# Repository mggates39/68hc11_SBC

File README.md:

# 68hc11_SBC   [![Badge License]][License]
Building a Single Board Computer around the MC68HC11.  Specifically the XC68HC11A1FN - A38P8642.  It will include my first attempt with [KiCad](https://www.kicad.org/) designing a PCB

[![Button Manual]][Manual]
[![Button Memory]][Memory]

Software built with [TASM](https://www.ticalc.org/archives/files/fileinfo/250/25051.html)

Run in the [68HC11 Simulator](http://www.hc11.demon.nl/thrsim11/thrsim11.htm)

<!----------------------------------[ File links ]--------------------------------->

[License]: LICENSE
[Manual]: Documentation/Reference/68hc11%20Technical%20Manual.pdf
[Memory]: Documentation/Memory%20Map.md

<!----------------------------------[ Badges ]--------------------------------->

[Badge License]: https://img.shields.io/badge/License-GPL3-015d93.svg?style=for-the-badge&labelColor=blue

<!---------------------------------[ Buttons ]--------------------------------->

[Button Manual]: https://img.shields.io/badge/User_Manual-4285F4?style=for-the-badge&logoColor=white&logo=GitBook
[Button Memory]: https://img.shields.io/badge/Memory_Map-0F9D58?style=for-the-badge&logoColor=white&logo=Fitbit

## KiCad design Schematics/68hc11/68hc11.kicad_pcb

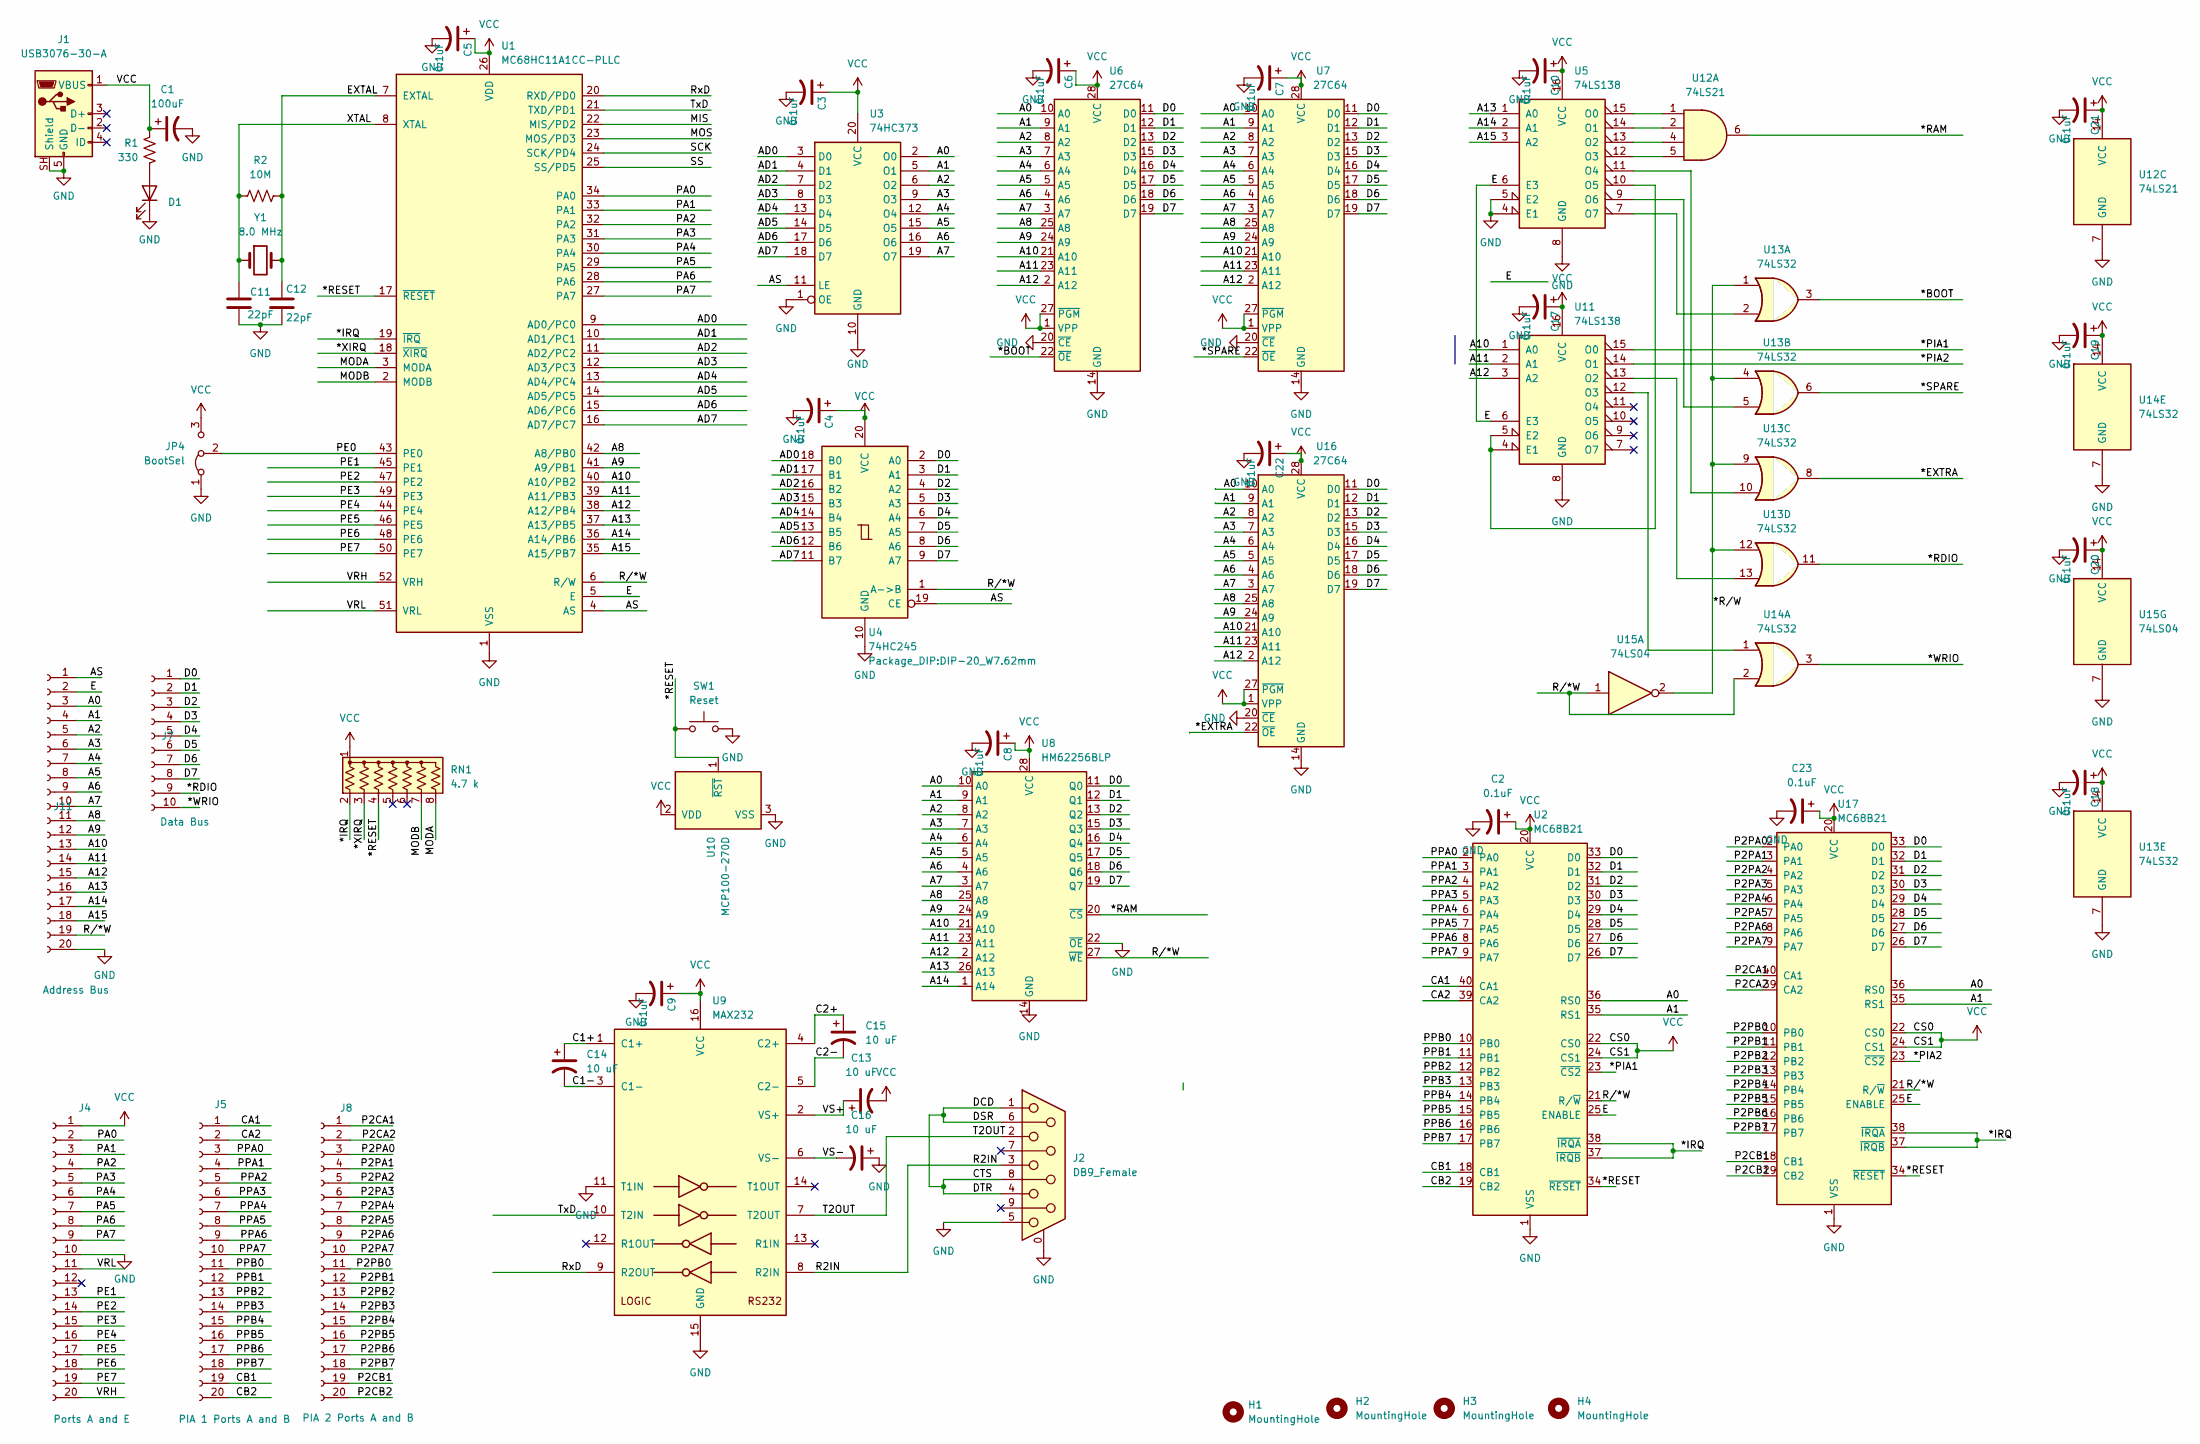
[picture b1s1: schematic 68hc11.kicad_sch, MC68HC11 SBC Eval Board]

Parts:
C1: 100uF; CP_Radial_D5.0mm_P2.00mm
C2, C3, C4, C5, C6, C7, C8, C9, C10, C17, C18, C19, C20, C21, C22, C23: 0.1uF; C_Disc_D3.0mm_W2.0mm_P2.50mm
C11, C12: 22pF; C_Disc_D3.0mm_W1.6mm_P2.50mm
C13, C14, C15, C16: 10 uF; CP_Radial_D5.0mm_P2.00mm
D1: LED; LED_D5.0mm
H1, H2, H3, H4: MountingHole; MountingHole_2.5mm
J1: USB3076-30-A; USB_Micro_B_Female_10118193-0001LF
J2: DB9_Female; DSUB-9_Male_Horizontal_P2.77x2.84mm_EdgePinOffset4.94mm_Hou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
J4: Ports A and E; PinSocket_1x20_P2.54mm_Vertical
J5: PIA 1 Ports A and B; PinSocket_1x20_P2.54mm_Vertical
J7: Data Bus; PinSocket_1x10_P2.54mm_Vertical
J8: PIA 2 Ports A and B; PinSocket_1x20_P2.54mm_Vertical
J11: Address Bus; PinSocket_1x20_P2.54mm_Vertical
JP4: BootSel; PinHeader_1x03_P2.54mm_Vertical
R1: 330; R_Axial_DIN0204_L3.6mm_D1.6mm_P5.08mm_Horizontal
R2: 10M; R_Axial_DIN0204_L3.6mm_D1.6mm_P5.08mm_Horizontal
RN1: 4.7 k; R_Array_SIP8
SW1: Reset; SW_PUSH_6mm
U1: MC68HC11A1CC-PLLC; PLCC-52_THT-Socket
U2, U17: MC68B21; DIP-40_W15.24mm
U3: 74HC373; DIP-20_W7.62mm
U4: 74HC245; DIP-20_W7.62mm
U5, U11: 74LS138; DIP-16_W7.62mm
U6, U7, U16: 27C64; DIP-28_W15.24mm
U8: HM62256BLP; DIP-28_W15.24mm
U9: MAX232; DIP-16_W7.62mm
U10: MCP100-270D; TO-92
U12: 74LS21; DIP-14_W7.62mm
U13, U14: 74LS32; DIP-14_W7.62mm
U15: 74LS04; DIP-14_W7.62mm
Y1: 8.0 MHz; Crystal_HC49-4H_Vertical

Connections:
/*BOOT: U6.22 (~OE), U13.3
/*EXTRA: U13.8, U16.22 (~OE)
/*IRQ: RN1.2 (R1), U1.19 (~IRQ), U2.37 (~IRQB), U2.38 (~IRQA), U17.37 (~IRQB), U17.38 (~IRQA)
/*PIA1: U2.23 (~CS2), U11.15 (O0)
/*PIA2: U11.14 (O1), U17.23 (~CS2)
/*RAM: U8.20 (~CS), U12.6
/*RDIO: U13.11
/*RESET: RN1.4 (R3), SW1.1, U1.17 (~RESET), U2.34 (~RESET), U10.1 (~RST), U17.34 (~RESET)
/*R/W: U13.1, U13.4, U13.9, U13.12, U15.2
/*SPARE: U7.22 (~OE), U13.6
/*WRIO: U14.3
/*XIRQ: RN1.3 (R2), U1.18 (~XIRQ)
/A0: J11.3, U2.36 (RS0), U3.2 (O0), U6.10 (A0), U7.10 (A0), U8.10 (A0), U16.10 (A0), U17.36 (RS0)
/A1: J11.4, U2.35 (RS1), U3.5 (O1), U6.9 (A1), U7.9 (A1), U8.9 (A1), U16.9 (A1), U17.35 (RS1)
/A2: J11.5, U3.6 (O2), U6.8 (A2), U7.8 (A2), U8.8 (A2), U16.8 (A2)
/A3: J11.6, U3.9 (O3), U6.7 (A3), U7.7 (A3), U8.7 (A3), U16.7 (A3)
/A4: J11.7, U3.12 (O4), U6.6 (A4), U7.6 (A4), U8.6 (A4), U16.6 (A4)
/A5: J11.8, U3.15 (O5), U6.5 (A5), U7.5 (A5), U8.5 (A5), U16.5 (A5)
/A6: J11.9, U3.16 (O6), U6.4 (A6), U7.4 (A6), U8.4 (A6), U16.4 (A6)
/A7: J11.10, U3.19 (O7), U6.3 (A7), U7.3 (A7), U8.3 (A7), U16.3 (A7)
/A8: J11.11, U1.42 (A8/PB0), U6.25 (A8), U7.25 (A8), U8.25 (A8), U16.25 (A8)
/A9: J11.12, U1.41 (A9/PB1), U6.24 (A9), U7.24 (A9), U8.24 (A9), U16.24 (A9)
/A10: J11.13, U1.40 (A10/PB2), U6.21 (A10), U7.21 (A10), U8.21 (A10), U11.1 (A0), U16.21 (A10)
/A11: J11.14, U1.39 (A11/PB3), U6.23 (A11), U7.23 (A11), U8.23 (A11), U11.2 (A1), U16.23 (A11)
/A12: J11.15, U1.38 (A12/PB4), U6.2 (A12), U7.2 (A12), U8.2 (A12), U11.3 (A2), U16.2 (A12)
/A13: J11.16, U1.37 (A13/PB5), U5.1 (A0), U8.26 (A13)
/A14: J11.17, U1.36 (A14/PB6), U5.2 (A1), U8.1 (A14)
/A15: J11.18, U1.35 (A15/PB7), U5.3 (A2)
/AD0: U1.9 (AD0/PC0), U3.3 (D0), U4.18 (B0)
/AD1: U1.10 (AD1/PC1), U3.4 (D1), U4.17 (B1)
/AD2: U1.11 (AD2/PC2), U3.7 (D2), U4.16 (B2)
/AD3: U1.12 (AD3/PC3), U3.8 (D3), U4.15 (B3)
/AD4: U1.13 (AD4/PC4), U3.13 (D4), U4.14 (B4)
/AD5: U1.14 (AD5/PC5), U3.14 (D5), U4.13 (B5)
/AD6: U1.15 (AD6/PC6), U3.17 (D6), U4.12 (B6)
/AD7: U1.16 (AD7/PC7), U3.18 (D7), U4.11 (B7)
/AS: J11.1, U1.4 (AS), U3.11 (LE), U4.19 (CE)
/C1+: C14.1, U9.1 (C1+)
/C1-: C14.2, U9.3 (C1-)
/C2+: C15.1, U9.4 (C2+)
/C2-: C15.2, U9.5 (C2-)
/CA1: J5.1, U2.40 (CA1)
/CA2: J5.2, U2.39 (CA2)
/CB1: J5.19, U2.18 (CB1)
/CB2: J5.20, U2.19 (CB2)
/CTS: J2.1, J2.4, J2.6, J2.8
/D0: J7.1, U2.33 (D0), U4.2 (A0), U6.11 (D0), U7.11 (D0), U8.11 (Q0), U16.11 (D0), U17.33 (D0)
/D1: J7.2, U2.32 (D1), U4.3 (A1), U6.12 (D1), U7.12 (D1), U8.12 (Q1), U16.12 (D1), U17.32 (D1)
/D2: J7.3, U2.31 (D2), U4.4 (A2), U6.13 (D2), U7.13 (D2), U8.13 (Q2), U16.13 (D2), U17.31 (D2)
/D3: J7.4, U2.30 (D3), U4.5 (A3), U6.15 (D3), U7.15 (D3), U8.15 (Q3), U16.15 (D3), U17.30 (D3)
/D4: J7.5, U2.29 (D4), U4.6 (A4), U6.16 (D4), U7.16 (D4), U8.16 (Q4), U16.16 (D4), U17.29 (D4)
/D5: J7.6, U2.28 (D5), U4.7 (A5), U6.17 (D5), U7.17 (D5), U8.17 (Q5), U16.17 (D5), U17.28 (D5)
/D6: J7.7, U2.27 (D6), U4.8 (A6), U6.18 (D6), U7.18 (D6), U8.18 (Q6), U16.18 (D6), U17.27 (D6)
/D7: J7.8, U2.26 (D7), U4.9 (A7), U6.19 (D7), U7.19 (D7), U8.19 (Q7), U16.19 (D7), U17.26 (D7)
/E: J11.2, U1.5 (E), U2.25 (ENABLE), U5.6 (E3), U11.6 (E3), U17.25 (ENABLE)
/EXTAL: C12.1, R2.1, U1.7 (EXTAL), Y1.2
/MIS: U1.22 (MIS/PD2)
/MODA: RN1.8 (R7), U1.3 (MODA)
/MODB: RN1.7 (R6), U1.2 (MODB)
/MOS: U1.23 (MOS/PD3)
/P2CA1: J8.1, U17.40 (CA1)
/P2CA2: J8.2, U17.39 (CA2)
/P2CB1: J8.19, U17.18 (CB1)
/P2CB2: J8.20, U17.19 (CB2)
/P2PA0: J8.3, U17.2 (PA0)
/P2PA1: J8.4, U17.3 (PA1)
/P2PA2: J8.5, U17.4 (PA2)
/P2PA3: J8.6, U17.5 (PA3)
/P2PA4: J8.7, U17.6 (PA4)
/P2PA5: J8.8, U17.7 (PA5)
/P2PA6: J8.9, U17.8 (PA6)
/P2PA7: J8.10, U17.9 (PA7)
/P2PB0: J8.11, U17.10 (PB0)
/P2PB1: J8.12, U17.11 (PB1)
/P2PB2: J8.13, U17.12 (PB2)
/P2PB3: J8.14, U17.13 (PB3)
/P2PB4: J8.15, U17.14 (PB4)
/P2PB5: J8.16, U17.15 (PB5)
/P2PB6: J8.17, U17.16 (PB6)
/P2PB7: J8.18, U17.17 (PB7)
/PA0: J4.2, U1.34 (PA0)
/PA1: J4.3, U1.33 (PA1)
/PA2: J4.4, U1.32 (PA2)
/PA3: J4.5, U1.31 (PA3)
/PA4: J4.6, U1.30 (PA4)
/PA5: J4.7, U1.29 (PA5)
/PA6: J4.8, U1.28 (PA6)
/PA7: J4.9, U1.27 (PA7)
/PE0: JP4.2 (C), U1.43 (PE0)
/PE1: J4.13, U1.45 (PE1)
/PE2: J4.14, U1.47 (PE2)
/PE3: J4.15, U1.49 (PE3)
/PE4: J4.16, U1.44 (PE4)
/PE5: J4.17, U1.46 (PE5)
/PE6: J4.18, U1.48 (PE6)
/PE7: J4.19, U1.50 (PE7)
/PPA0: J5.3, U2.2 (PA0)
/PPA1: J5.4, U2.3 (PA1)
/PPA2: J5.5, U2.4 (PA2)
/PPA3: J5.6, U2.5 (PA3)
/PPA4: J5.7, U2.6 (PA4)
/PPA5: J5.8, U2.7 (PA5)
/PPA6: J5.9, U2.8 (PA6)
/PPA7: J5.10, U2.9 (PA7)
/PPB0: J5.11, U2.10 (PB0)
/PPB1: J5.12, U2.11 (PB1)
/PPB2: J5.13, U2.12 (PB2)
/PPB3: J5.14, U2.13 (PB3)
/PPB4: J5.15, U2.14 (PB4)
/PPB5: J5.16, U2.15 (PB5)
/PPB6: J5.17, U2.16 (PB6)
/PPB7: J5.18, U2.17 (PB7)
/R2IN: J2.3, U9.8 (R2IN)
/RxD: U1.20 (RXD/PD0), U9.9 (R2OUT)
/R/*W: J11.19, U1.6 (R/W), U2.21 (R/~W), U4.1 (A->B), U8.27 (~WE), U14.2, U15.1, U17.21 (R/~W)
/SCK: U1.24 (SCK/PD4)
/SS: U1.25 (SS/PD5)
/T2OUT: J2.2, U9.7 (T2OUT)
/TxD: U1.21 (TXD/PD1), U9.10 (T2IN)
/VRH: J4.20, U1.52 (VRH)
/VRL: J4.11, U1.51 (VRL)
/VS+: C13.1, U9.2 (VS+)
/VS-: C16.2, U9.6 (VS-)
/XTAL: C11.1, R2.2, U1.8 (XTAL), Y1.1
GND: C1.2, C2.2, C3.2, C4.2, C5.2, C6.2, C7.2, C8.2, C9.2, C10.2, C11.2, C12.2, C16.1, C17.2, C18.2, C19.2, C20.2, C21.2, C22.2, C23.2, D1.1 (K), J1.5 (GND), J1.SH (Shield), J2.0 (PAD), J2.5, J4.10, J11.20, JP4.1 (A), SW1.2, U1.1 (VSS), U2.1 (VSS), U3.1 (OE), U3.10 (GND), U4.10 (GND), U5.4 (E1), U5.5 (E2), U5.8 (GND), U6.14 (GND), U6.20 (~CE), U7.14 (GND), U7.20 (~CE), U8.14 (GND), U8.22 (~OE), U9.11 (T1IN), U9.15 (GND), U10.3 (VSS), U11.8 (GND), U12.7 (GND), U13.7 (GND), U14.7 (GND), U15.7 (GND), U16.14 (GND), U16.20 (~CE), U17.1 (VSS)
unnamed: D1.2 (A), R1.1
unnamed: U5.10 (O5), U11.4 (E1), U11.5 (E2)
unnamed: U11.12 (O3), U14.1
unnamed: U11.13 (O2), U13.13
unnamed: U5.15 (O0), U12.1
unnamed: U5.14 (O1), U12.2
unnamed: U5.13 (O2), U12.4
unnamed: U5.12 (O3), U12.5
unnamed: U5.7 (O7), U13.2
unnamed: U5.9 (O6), U13.5
unnamed: U5.11 (O4), U13.10
VCC: C1.1, C2.1, C3.1, C4.1, C5.1, C6.1, C7.1, C8.1, C9.1, C10.1, C13.2, C17.1, C18.1, C19.1, C20.1, C21.1, C22.1, C23.1, J1.1 (VBUS), J4.1, JP4.3 (B), R1.2, RN1.1 (common), U1.26 (VDD), U2.20 (VCC), U2.22 (CS0), U2.24 (CS1), U3.20 (VCC), U4.20 (VCC), U5.16 (VCC), U6.1 (VPP), U6.27 (~PGM), U6.28 (VCC), U7.1 (VPP), U7.27 (~PGM), U7.28 (VCC), U8.28 (VCC), U9.16 (VCC), U10.2 (VDD), U11.16 (VCC), U12.14 (VCC), U13.14 (VCC), U14.14 (VCC), U15.14 (VCC), U16.1 (VPP), U16.27 (~PGM), U16.28 (VCC), U17.20 (VCC), U17.22 (CS0), U17.24 (CS1)

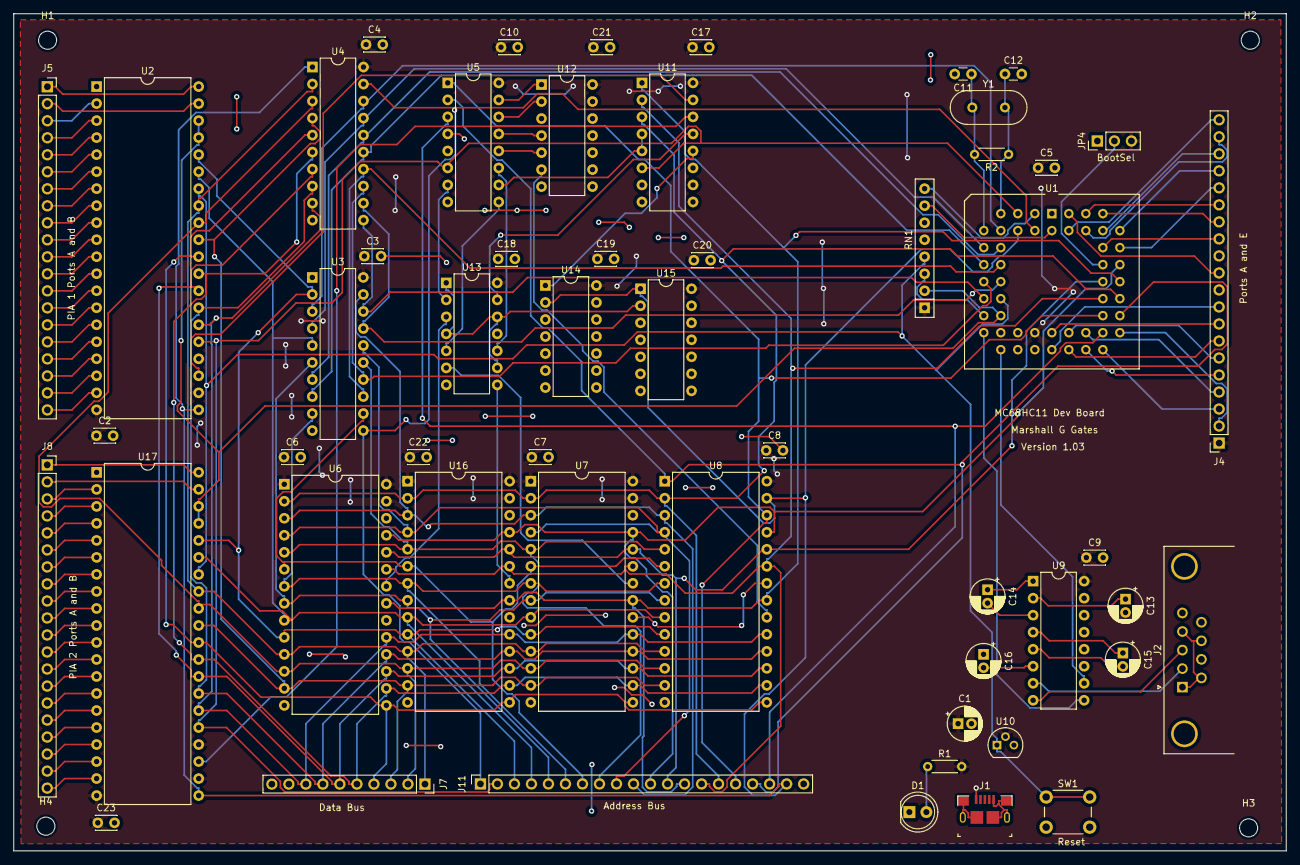
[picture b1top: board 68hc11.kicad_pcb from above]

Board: 2 copper layers, 190.0 x 125.0 mm, 58 parts (0 on the bottom side), 131 nets.

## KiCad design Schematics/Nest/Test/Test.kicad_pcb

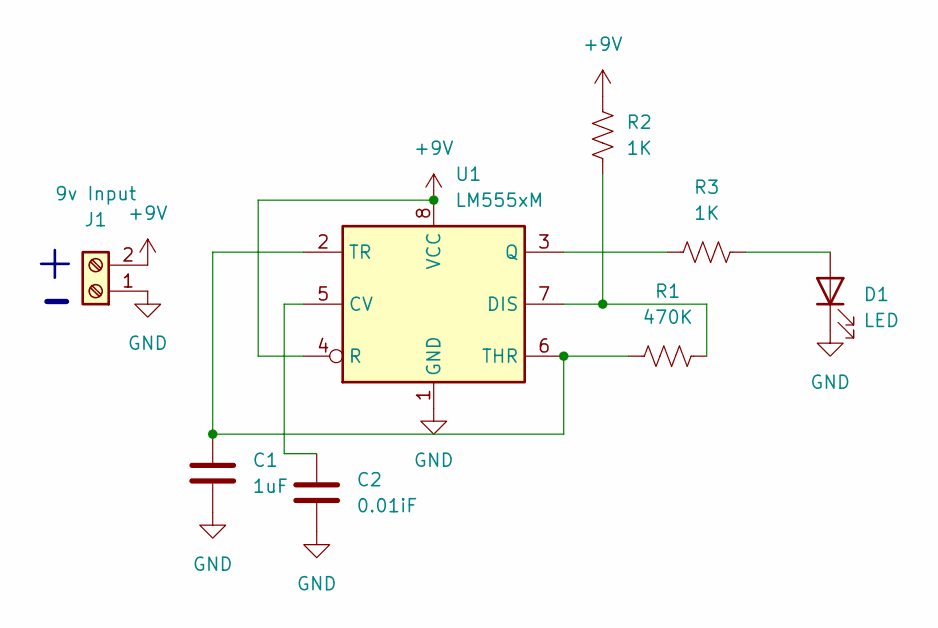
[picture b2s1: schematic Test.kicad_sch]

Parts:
C1: 1uF; C_Disc_D5.0mm_W2.5mm_P2.50mm
C2: 0.01iF; C_Disc_D5.0mm_W2.5mm_P2.50mm
D1: LED; LED_D5.0mm
J1: 9v Input; TerminalBlock_bornier-2_P5.08mm
R1: 470K; R_Axial_DIN0207_L6.3mm_D2.5mm_P10.16mm_Horizontal
R2, R3: 1K; R_Axial_DIN0207_L6.3mm_D2.5mm_P10.16mm_Horizontal
U1: LM555xM; DIP-8_W7.62mm

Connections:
+9V: J1.2, R2.1, U1.4 (R), U1.8 (VCC)
GND: C1.2, C2.2, D1.1 (K), J1.1, U1.1 (GND)
unnamed: D1.2 (A), R3.2
unnamed: R3.1, U1.3 (Q)
unnamed: C2.1, U1.5 (CV)
unnamed: C1.1, R1.1, U1.2 (TR), U1.6 (THR)
unnamed: R1.2, R2.2, U1.7 (DIS)

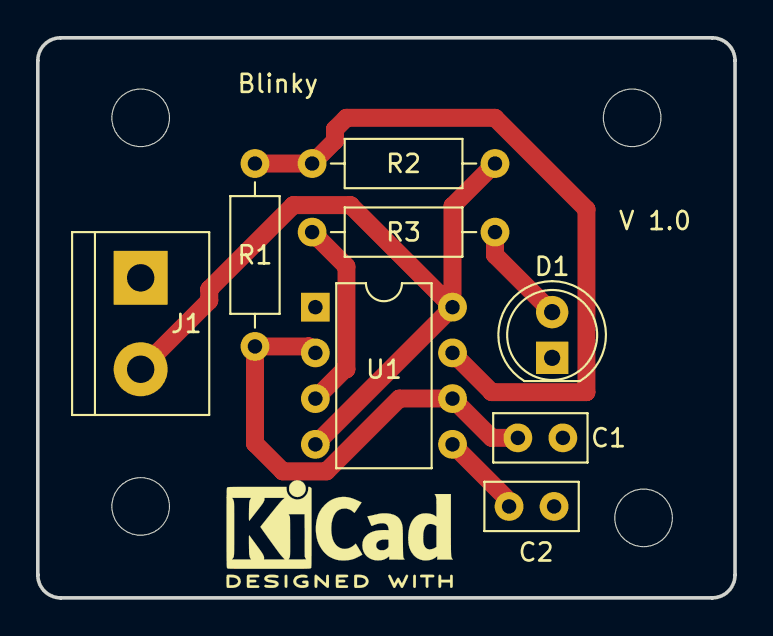
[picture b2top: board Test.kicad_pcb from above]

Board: 2 copper layers, 38.7 x 31.1 mm, 8 parts (0 on the bottom side), 7 nets.

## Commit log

2022-08-02 Adding Datasheets and Users Guides
    Datasheets and user guides from various on-line sources
2022-08-02 Adding the initial KiCad schematics
    Just dropped some components on the board. So much left to do.
2022-08-02 Added TASM development environment
2022-08-02 Added Buffalo Monitor Reference Manual
2022-08-02 Initial memory map
2022-08-03 Added source for Buffalo Monitor ROM
2022-08-03 Add ASM port definitions
2022-08-03 Assembedl Buffalo 3.4
2022-08-03 Add some more datasheets
2022-08-03 Start working on Address Block Decoding
    This is based on the needs of the Buffalo Monitor
2022-08-03 Start wiring components
2022-08-04 Updated Readme
    Converted memory map to markdown and adding another reference document
2022-08-05 Added some more chips to design
    Need to finish Addres block decoding soon.
2022-08-05 Added more components to schematic
2022-08-05 Added another power monitor datasheet
2022-08-05 Added some more reference documents
2022-08-05 Added MAX232 and DB9 for serial comms
2022-08-06 Added Crystal and some trace routing
2022-08-06 Added low power reset and cleaned up busses
2022-08-06 Addes a sample board all the way to gerbers
2022-08-06 Traced Data Bus between ROM, RAM and PCIA
2022-08-07 Traced out some more of the address bus
2022-08-07 Added Screw Terminals for IO Ports
2022-08-07 Added new reference documentation
2022-08-07 Added bypass caps to chips
2022-08-07 Cleaned up AD traces and all warnings
2022-08-07 removed unused backup files
2022-08-08 Added power jack
2022-08-08 Connected expansion port A
2022-08-09 Still working on traces
2022-08-09 Updated bad component values
    Also generated first Bill Of Materials
2022-08-10 Reset trace routing
    Start work on memory address decode logic
2022-08-12 Continueing to rework traces
    Addec VCC Plane
2022-08-13 Refine memory map
    Get the address decode logic worked out in design
2022-08-13 Playing with free routing tool
    ripped it all out when finished
    Still need to add address decode hardware then try again.
2022-08-14 Added address logic chips
    Next is layout
2022-08-14 Replaced screw terminals with pin headers
2022-08-14 Anouther autorouting attempt
2022-08-14 Updated chip footprints and generated new vBOM
2022-08-14 Updated power to micro usb b receptical
2022-08-15 yET ANOTHER LAYOUT AND ROUTING
2022-08-19 Restarting the board layout
2022-08-19 Another attempted layout
2022-08-20 Still working on it
2022-08-20 Added the Extra ROM Scocket
2022-08-21 Added second PIO chip socket
2022-08-21 Wired Data Bus
    Corrected discrepency between pin sockets and footprints turned 2 10 pin into 1 20 socket
2022-08-22 Wired ROM Chip Selects
2022-08-22 Reverted symbols to library standard
2022-08-23 Trying 4 layer board design
2022-08-25 Making progress in the routing
2022-08-26 More progress
2022-08-26 Getting closer
2022-08-27 A few more traces
    and one bodge trace and via
2022-08-28 Backup and punt again
2022-08-29 Board fully traced
    Ran Freetrace and then added nodge patches to fixx islands
2022-08-29 Updated ..gitignore for kicad
2022-08-29 Added missing silkscreen text
2022-08-29 Added PDF of schematic
2022-08-29 Added HTML BOM
2022-08-29 Clean up paper size and page titles
2022-08-30 Making a smaller board layout
2022-08-31 Rerouting board
    Generated new Dynamic BOM
2022-08-31 Finished routing smaller board
2022-09-01 Added mounting holes
    Added board name and version to silkscreen
    Generated new PDF, BOM and Gerbers
2022-09-01 Updated gitignore to allow latest gerber files
    Just not any of the versioned zip files
2022-09-03 Cleanup schematic layout
2022-09-13 Added images for blog notes
2022-09-13 Added board image
2022-09-25 Moved RAM ~CS lable
2022-09-29 Added third party 3d models
    For processor socket as the Package_LLC 3d shape folder is missing
    For micro usb b socket, but it doesn't show up
2022-11-10 Fixed typo in readme
2022-11-10 Fixed mounting hole size
2022-11-10 Correctly fixed mounting hole size
    Did it with the footprint like you are supposed to do.
